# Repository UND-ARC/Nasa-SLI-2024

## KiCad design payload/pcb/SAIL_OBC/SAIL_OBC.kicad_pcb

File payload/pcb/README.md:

# SAIL PCBs

## Files included
- KiCad project file (.kicad_pro)
- KiCad schematic (.kicad_sch) 
- KiCad layout (.kicad_pcb)
- 3D view PNG
- Schematic PDF
- Layout PNG
- Interactive Bill of Materials (.html)

### Onboard Computer (OBC)
- Teensy Microcontroller 
- Sensors
- ESC connectors
- 4-pin JST connector to GPS
- 6-pin JST connector to PDB

### Power Distribution Board (PDB)
- Power input
- 5V and 3.3V Buck Regulators
- External Power Switchj
- Arming Switch
- Pyro Charges
	- Landing Legs
	- Wire Cutter 1
	- Wire Cutter 2
- VCC, 5V, 3.3V, and GND test points
- 6 pin JST connector to OBC

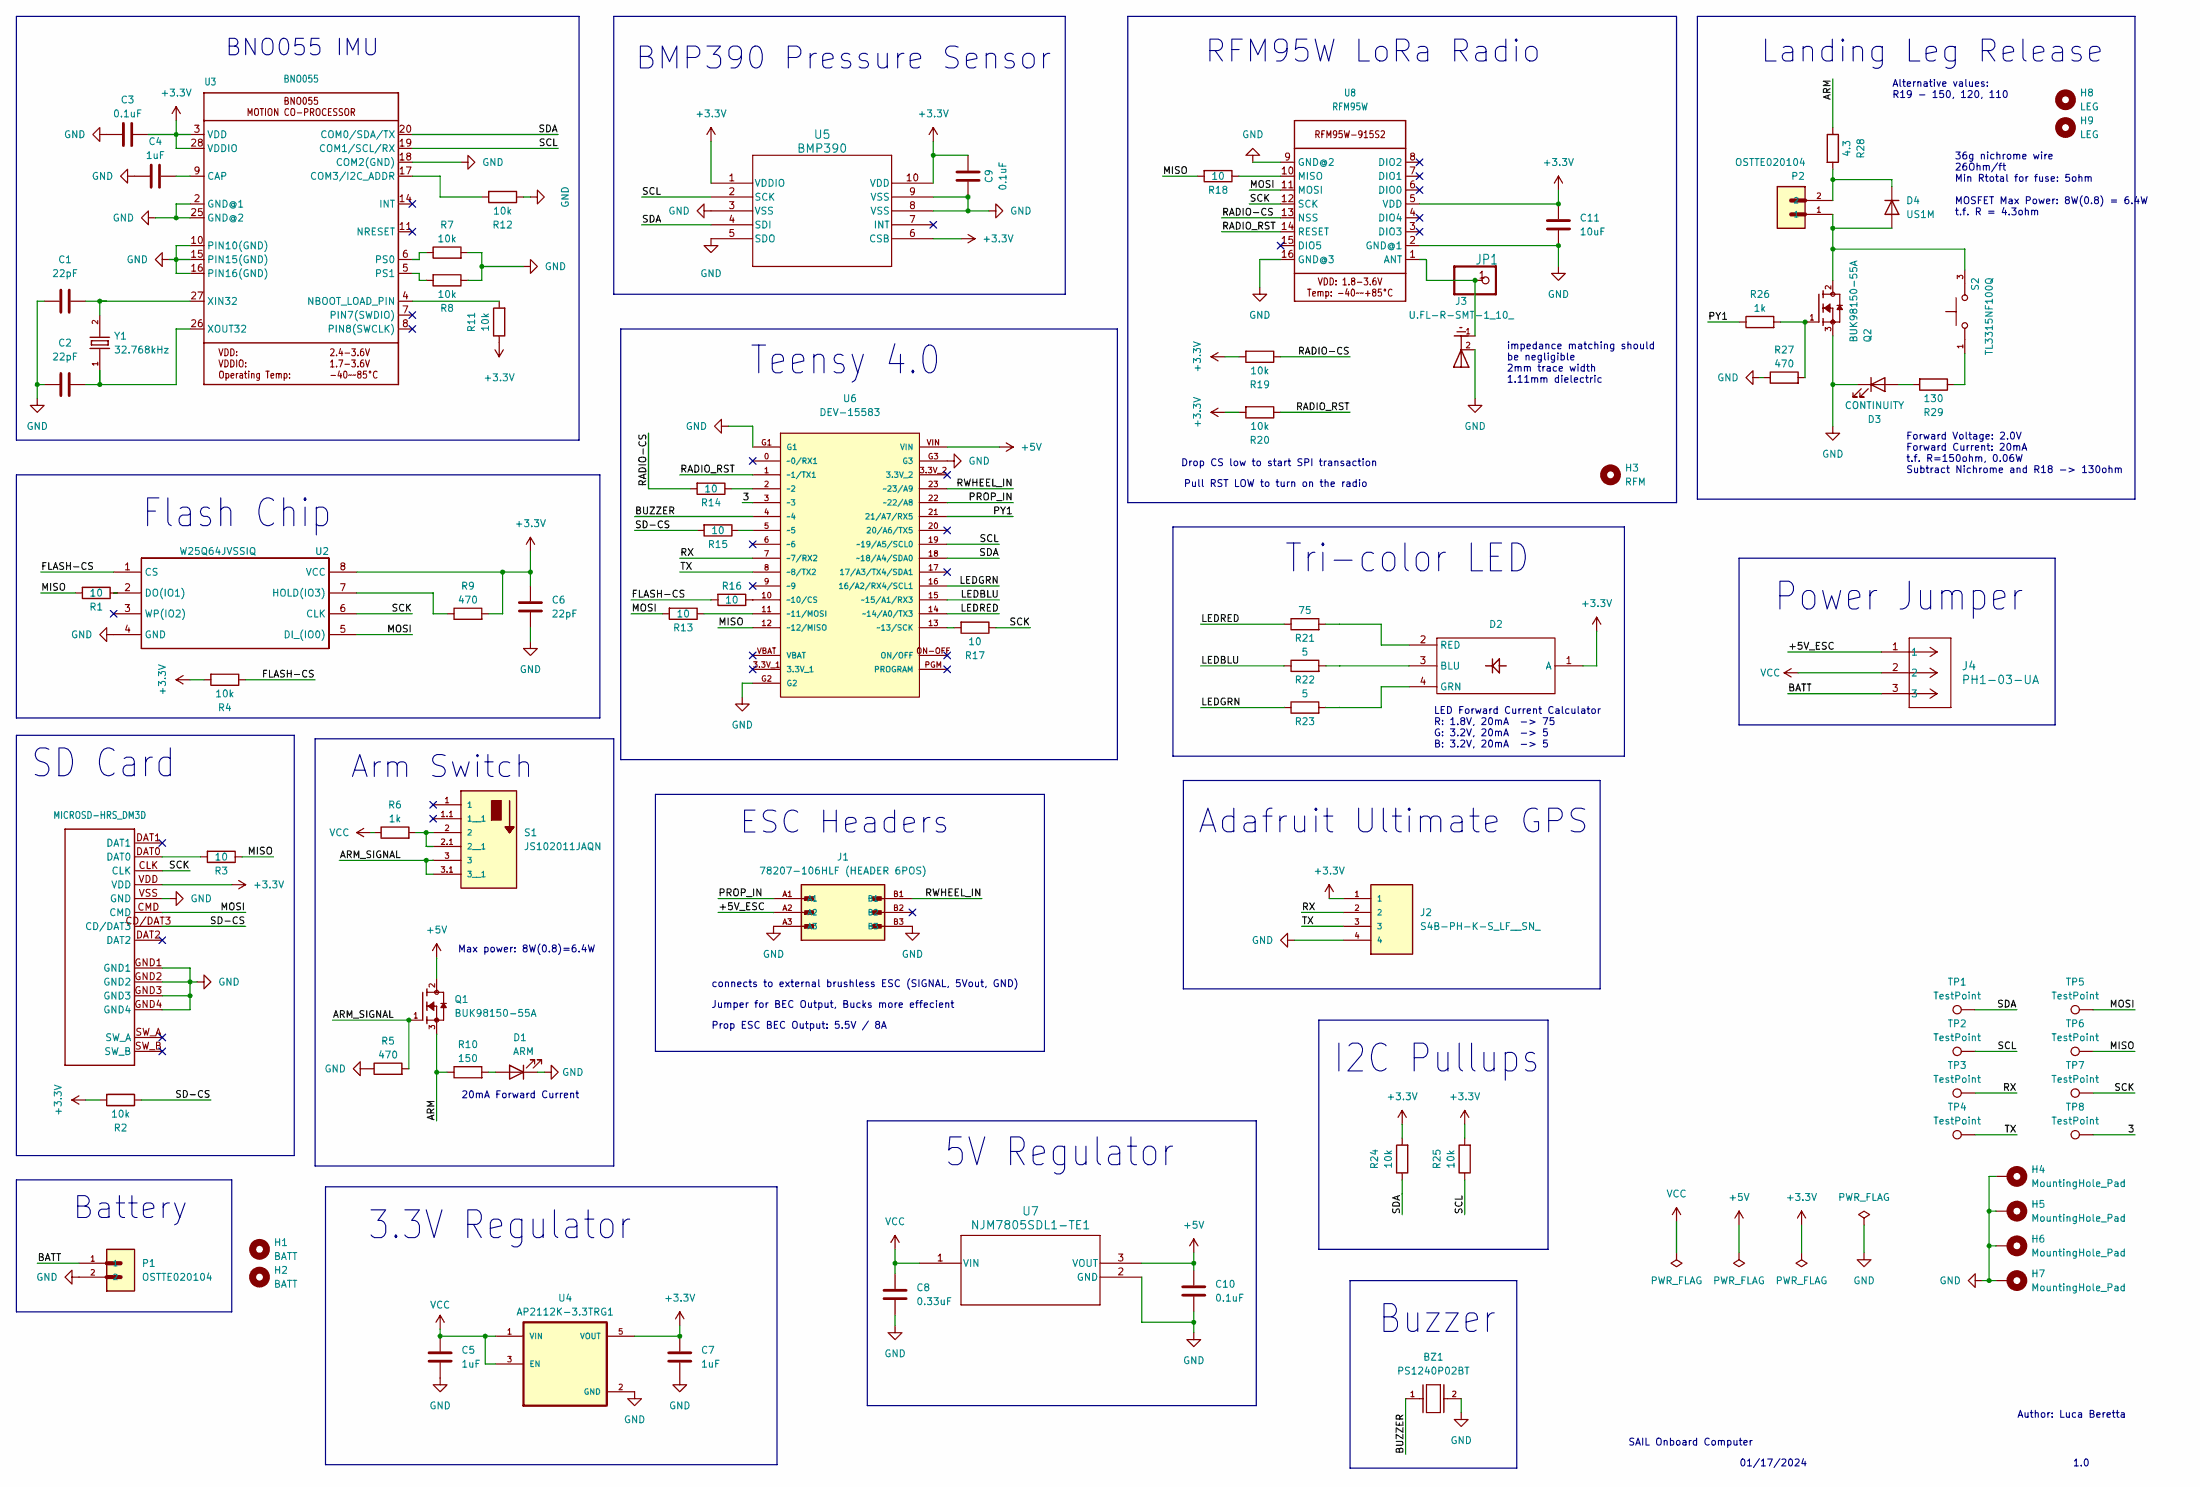
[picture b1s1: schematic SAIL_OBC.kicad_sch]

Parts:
BZ1: PS1240P02BT; BUZZER_XDCR_PS1240P02BT
C1, C2, C6: 22pF; 0805-NO (Capacitor)
C3, C9, C10: 0.1uF; 0805-NO (Capacitor)
C4, C5, C7: 1uF; 0805-NO (Capacitor)
C8: 0.33uF; 0805-NO (Capacitor)
C11: 10uF; 0805-NO (Capacitor)
D1: ARM; LED0805N_CML_(CMD17-21VRDTR8)
D2: TRI-COLOR LED; LED_D5.0mm-4_RGB
D3: CONTINUITY; LED0805N_CML_(CMD17-21VRDTR8)
D4: US1M; D_SMA
H1, H2: BATT; MountingHole_2.7mm_M2.5_ZIPTIE
H3: RFM; MountingHole_2.7mm_M2.5_ZIPTIE
H4, H5, H6, H7: MountingHole_Pad; MountingHole_3mm_Pad
H8, H9: LEG; MountingHole_2.7mm_M2.5_ZIPTIE
J1: 78207-106HLF (HEADER 6POS); AMPHENOL_78207-106HLF
J2: S4B-PH-K-S_LF__SN_; JST_S4B-PH-K-S_LF__SN_
J3: U.FL-R-SMT-1_10_; CONN1_UFL-R_HIR
J4: PH1-03-UA; PinHeader_1x3_P2.54_Drill1.1mm
JP1: HEADER-1X1ROUND; 1X01_ROUND
P1, P2: OSTTE020104; TERMBLOCK_OSTTE020104_3_5MM
Q1, Q2: BUK98150-55A; BUK98150-55ACUF
R1, R3, R13, R14, R15, R16, R17, R18: 10; R_0603_1608Metric_Pad0.98x0.95mm_HandSolder
R2, R7, R8, R11, R12, R19, R20, R24, R25: 10k; 0805-NO-Resistor
R4: 10k; R_0603_1608Metric_Pad0.98x0.95mm_HandSolder
R5, R9, R27: 470; 0805-NO-Resistor
R6, R26: 1k; 0805-NO-Resistor
R10: 150; 0805-NO-Resistor
R21: 75; 0805-NO-Resistor
R22, R23: 5; 0805-NO-Resistor
R28: 4.3; RESC6331X65N
R29: 130; 0805-NO-Resistor
S1: JS102011JAQN; SW_JS102011JAQN
S2: TL3315NF100Q; SW_TL3315NF100Q
TP1, TP2, TP3, TP4, TP5, TP6, TP7, TP8: TestPoint; TestPoint_Pad_2.0x2.0mm
U1: MICROSD-HRS_DM3D
U2: W25Q64JVSSIQ
U3: BNO055; BNO055_SMT
U4: AP2112K-3.3TRG1; SOT95P285X140-5N
U5: BMP390; LGA10_BMP390_BOS
U6: DEV-15583; MODULE_DEV-15583
U7: NJM7805SDL1-TE1; TO-252-3-L1_NMD
U8: RFM95W; RFMHCW_SMT
Y1: 32.768kHz; CRYSTAL_ECS-.327-12.5-34B-TR

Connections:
+3.3V: C3.2, C6.1, C7.1, C9.2, C11.2, D2.1 (A), J2.1, R2.2, R4.2, R9.2, R11.1, R19.2, R20.2, R24.2, R25.2, U1.VDD, U2.8 (VCC), U3.3 (VDD), U3.28 (VDDIO), U4.5 (VOUT), U5.1 (VDDIO), U5.6 (CSB), U5.10 (VDD), U8.5 (VDD)
+5V: C10.2, Q1.2, U6.VIN, U7.3 (VOUT)
/3: TP8.1, U6.3 (~3)
/+5V_ESC: J1.A2, J4.1
/ARM: Q1.3, R10.1, R28.1
/ARM_SIGNAL: Q1.1, R5.2, S1.3, S1.3.1 (3__1)
/BATT: J4.3, P1.1
/BUZZER: BZ1.1, U6.4 (~4)
/FLASH-CS: R4.1, R16.2, U2.1 (CS)
/LEDBLU: R22.1, U6.15 (~15/A1/RX3)
/LEDGRN: R23.1, U6.16 (16/A2/RX4/SCL1)
/LEDRED: R21.1, U6.14 (~14/A0/TX3)
/MISO: R1.2, R3.1, R18.2, TP6.1, U6.12 (~12/MISO)
/MOSI: R13.2, TP5.1, U1.CMD, U2.5 (DI_(IO0)), U8.11 (MOSI)
/PROP_IN: J1.A1, U6.22 (~22/A8)
/PY1: R26.1, U6.21 (21/A7/RX5)
/RADIO-CS: R14.2, R19.1, U8.13 (NSS)
/RADIO_RST: R20.1, U6.1 (~1/TX1), U8.14 (RESET)
/RWHEEL_IN: J1.B1, U6.23 (~23/A9)
/RX: J2.2, TP3.1, U6.7 (~7/RX2)
/SCK: R17.1, TP7.1, U1.CLK, U2.6 (CLK), U8.12 (SCK)
/SCL: R25.1, TP2.1, U3.19 (COM1/SCL/RX), U5.2 (SCK), U6.19 (~19/A5/SCL0)
/SD-CS: R2.1, R15.2, U1.CD/DAT3
/SDA: R24.1, TP1.1, U3.20 (COM0/SDA/TX), U5.4 (SDI), U6.18 (~18/A4/SDA0)
/TX: J2.3, TP4.1, U6.8 (~8/TX2)
GND: BZ1.2, C1.1, C2.1, C3.1, C4.1, C5.2, C6.2, C7.2, C8.1, C9.1, C10.1, C11.1, D1.1 (K), D3.1 (K), H4.1, H5.1, H6.1, H7.1, J1.A3, J1.B3, J2.4, J3.2, P1.2, Q2.3, R5.1, R7.2, R8.1, R12.1, R27.1, U1.GND1, U1.GND2, U1.GND3, U1.GND4, U1.VSS (GND), U2.4 (GND), U3.2 (GND@1), U3.10 (PIN10(GND)), U3.15 (PIN15(GND)), U3.16 (PIN16(GND)), U3.18 (COM2(GND)), U3.25 (GND@2), U4.2 (GND), U5.3 (VSS), U5.5 (SDO), U5.8 (VSS), U5.9 (VSS), U6.G1, U6.G2, U6.G3, U7.2 (GND), U8.2 (GND@1), U8.9 (GND@2), U8.16 (GND@3)
unnamed: D1.2 (A), R10.2
unnamed: D2.3 (BLU), R22.2
unnamed: D2.4 (GRN), R23.2
unnamed: D2.2 (RED), R21.2
unnamed: D3.2 (A), R29.2
unnamed: D4.2 (A), P2.1, Q2.2, S2.3
unnamed: D4.1 (K), P2.2, R28.2
unnamed: Q2.1, R26.2, R27.2
unnamed: R3.2, U1.DAT0
unnamed: R29.1, S2.1
unnamed: R6.2, S1.2, S1.2.1 (2__1)
unnamed: R1.1, U2.2 (DO(IO1))
unnamed: R9.1, U2.7 (HOLD(IO3))
unnamed: C4.2, U3.9 (CAP)
unnamed: R12.2, U3.17 (COM3/I2C_ADDR)
unnamed: R11.2, U3.4 (NBOOT_LOAD_PIN)
unnamed: R7.1, U3.6 (PS0)
unnamed: R8.2, U3.5 (PS1)
unnamed: C1.2, U3.27 (XIN32), Y1.2
unnamed: C2.2, U3.26 (XOUT32), Y1.1
unnamed: R14.1, U6.2 (~2)
unnamed: R15.1, U6.5 (~5)
unnamed: R16.1, U6.10 (~10/CS)
unnamed: R13.1, U6.11 (~11/MOSI)
unnamed: R17.2, U6.13 (~13/SCK)
unnamed: J3.1, JP1.1, U8.1 (ANT)
unnamed: R18.1, U8.10 (MISO)
VCC: C5.1, C8.2, J4.2, R6.1, U4.1 (VIN), U4.3 (EN), U7.1 (VIN)

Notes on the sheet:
3.3V Regulator
Alternative values: R19 - 150, 120, 110
Prop ESC BEC Output: 5.5V / 8A
Max power: 8W(0.8)=6.4W
36g nichrome wire 26Ohm/ft Min Rtotal for fuse: 5ohm MOSFET Max Power: 8W(0.8) = 6.4W t.f. R = 4.3ohm
Flash Chip
BMP390 Pressure Sensor
Battery
Author: Luca Beretta
Buzzer
connects to external brushless ESC (SIGNAL, 5Vout, GND)
SD Card
5V Regulator
LED Forward Current Calculator R: 1.8V, 20mA -> 75 G: 3.2V, 20mA -> 5 B: 3.2V, 20mA -> 5
01/17/2024
Teensy 4.0
Drop CS low to start SPI transaction
Forward Voltage: 2.0V Forward Current: 20mA t.f. R=150ohm, 0.06W Subtract Nichrome and R18 -> 130ohm
Power Jumper
ESC Headers
1.0
BNO055 IMU
SAIL Onboard Computer
RFM95W LoRa Radio
impedance matching should be negligible 2mm trace width 1.11mm dielectric
Arm Switch
Jumper for BEC Output, Bucks more effecient
Pull RST LOW to turn on the radio
Adafruit Ultimate GPS
Landing Leg Release
20mA Forward Current
I2C Pullups
Tri-color LED

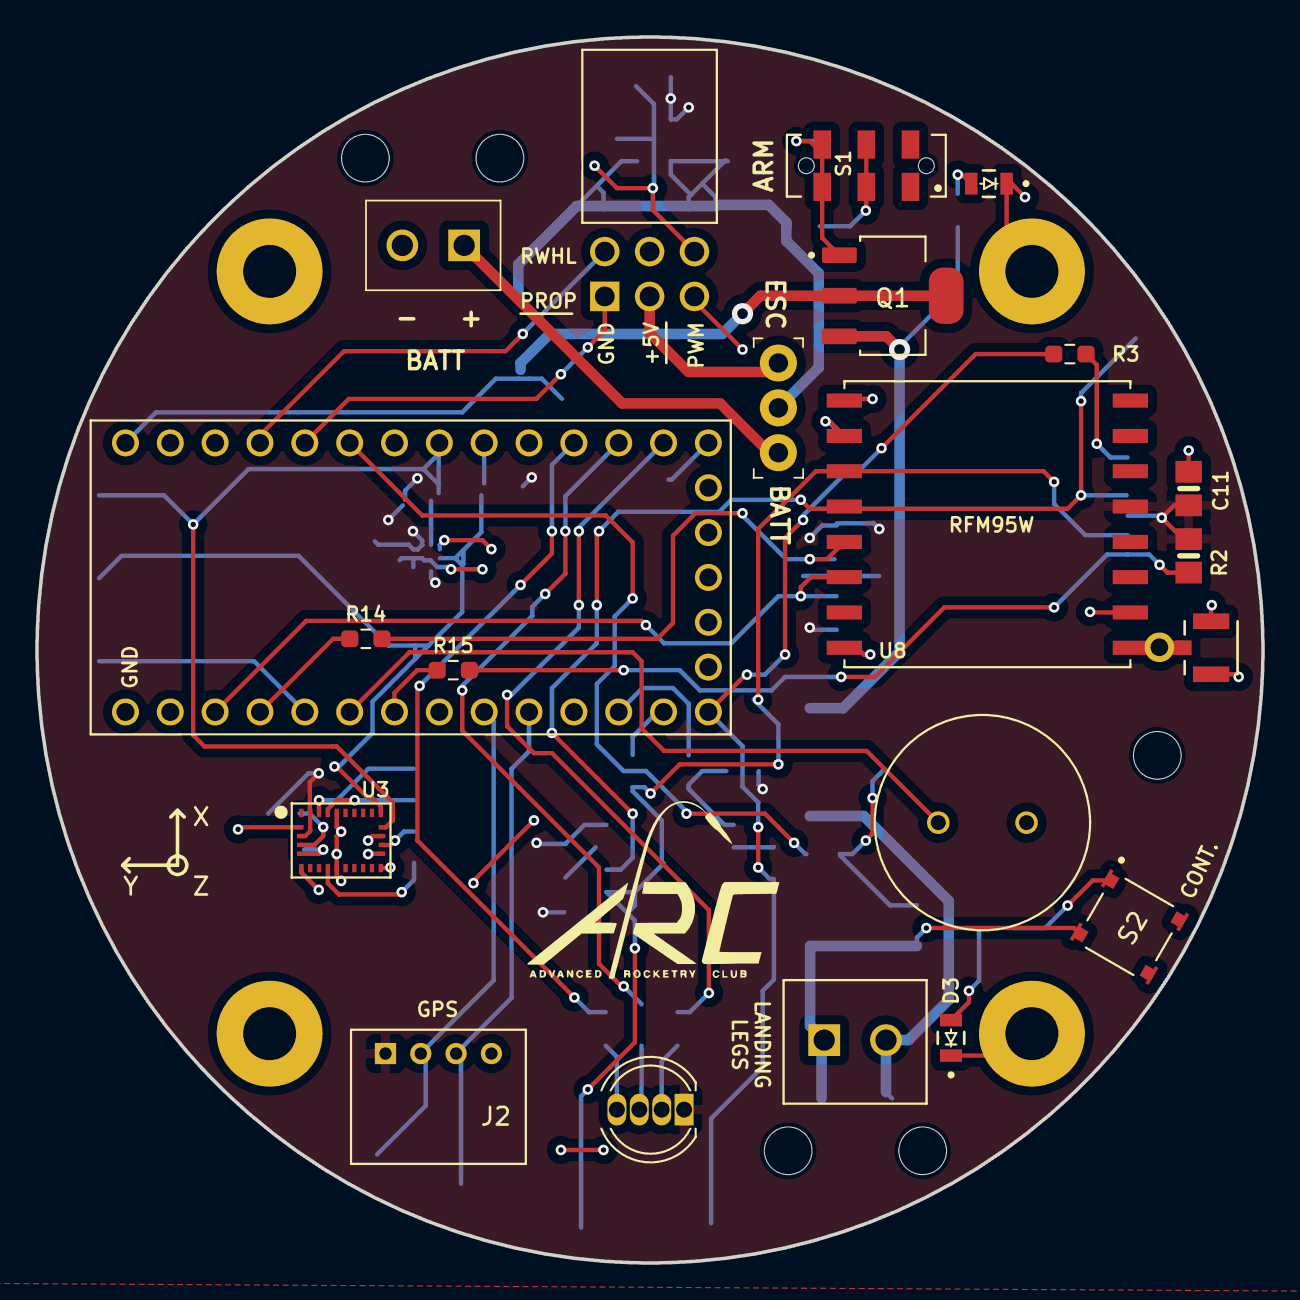
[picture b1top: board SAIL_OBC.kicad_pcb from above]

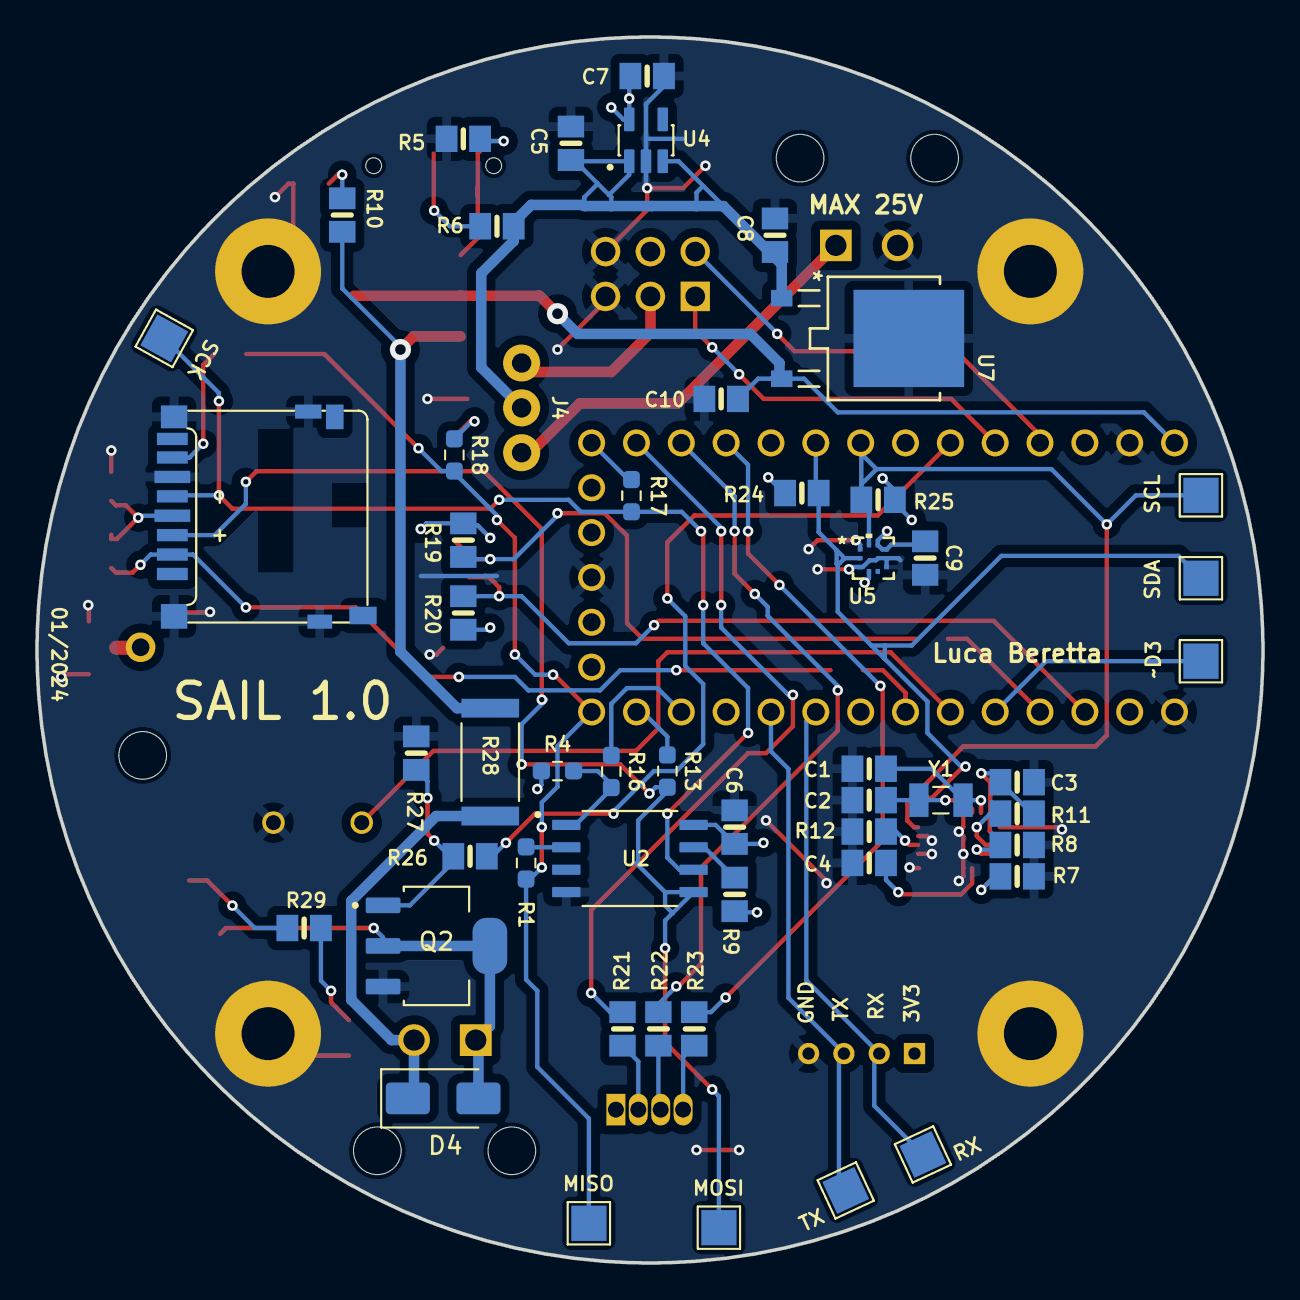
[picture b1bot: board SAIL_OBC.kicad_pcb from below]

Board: 2 copper layers, 69.4 x 69.4 mm, 82 parts (51 on the bottom side), 54 nets.

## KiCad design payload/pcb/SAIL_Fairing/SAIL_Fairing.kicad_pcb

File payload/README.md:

# STEMnauts Atmosphere Independent Lander (SAIL)

UND ARC SAIL Payload Module

## NASA Student Launch Objective

SAIL is an in-air deployable payload capable of safely retaining and recovering a group of 4 STEMnauts in a unique predetermined orientation without the use of a parachute or streamer or chemical energetics below 500 ft AGL. The landing shall occur under acceptable descent and landing parameters for the safe recovery of human beings.

## Description

The Advanced Rocketry Club of the University of North Dakota is designing a UAS-style payload that will deploy upon descent, autonomously land under acceptable parameters, and log flight data. The final electronics package shall be a custom 2x2 in Printed Circuit Board (PCB) that will be mounted on the SAIL payload with various connections to the battery, safety switch, landing leg release, and Electronic Speed Controllers (ESCs).

## Getting Started

### Hardware
- Teensy 4.0 Microcontroller
- BNO055 IMU
- BMP390 Pressure Sensor
- SPI Flash Chip
- MicroSD Card Holder
- Adafruit Ultimate GPS
- RFM95W 915MHz Radio Transceiver
- Xnova 4025 1120 KV Brushless Motor
- iFlight XING-E Pro 2207 1800KV Brushless Motor
- V-Good RC 32-Bit 120A 2-8S Brushless ESC
- Lumenier 36A BLHeli_32 32bit ESC
- 9V Battery
- 6S 2200mAh LiPo Battery

### Software
- C++ w/ Arduino IDE
- PCB designed in KiCad 7.0

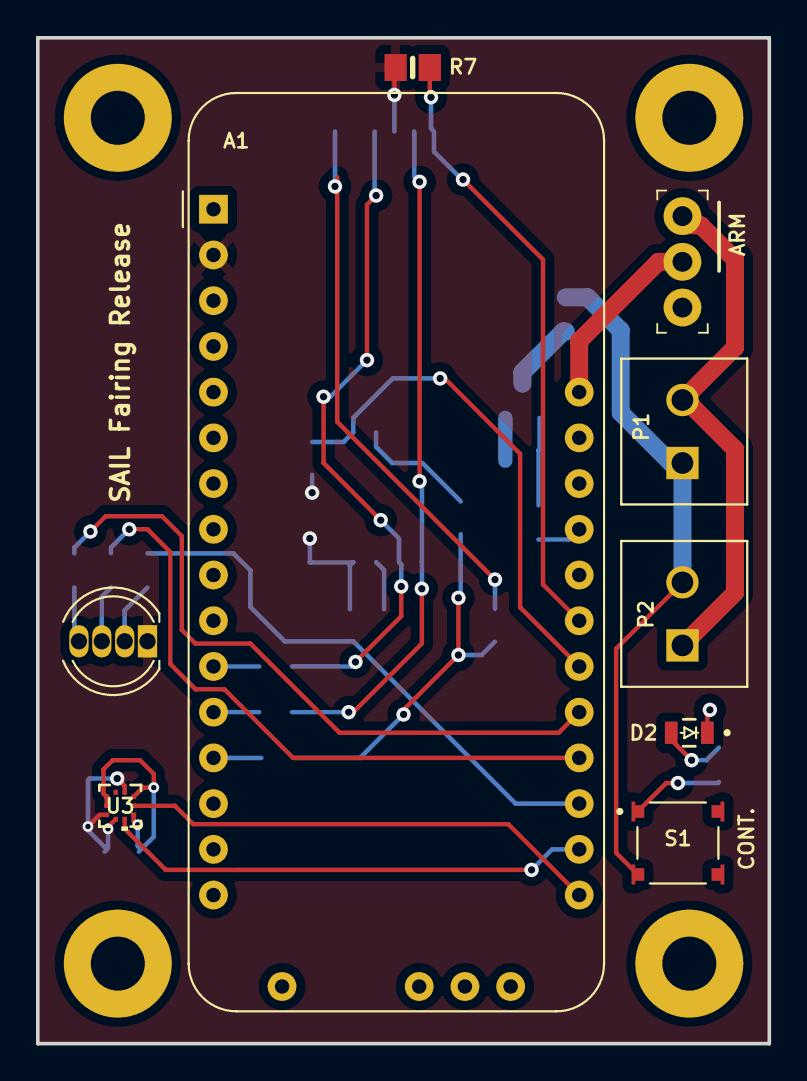
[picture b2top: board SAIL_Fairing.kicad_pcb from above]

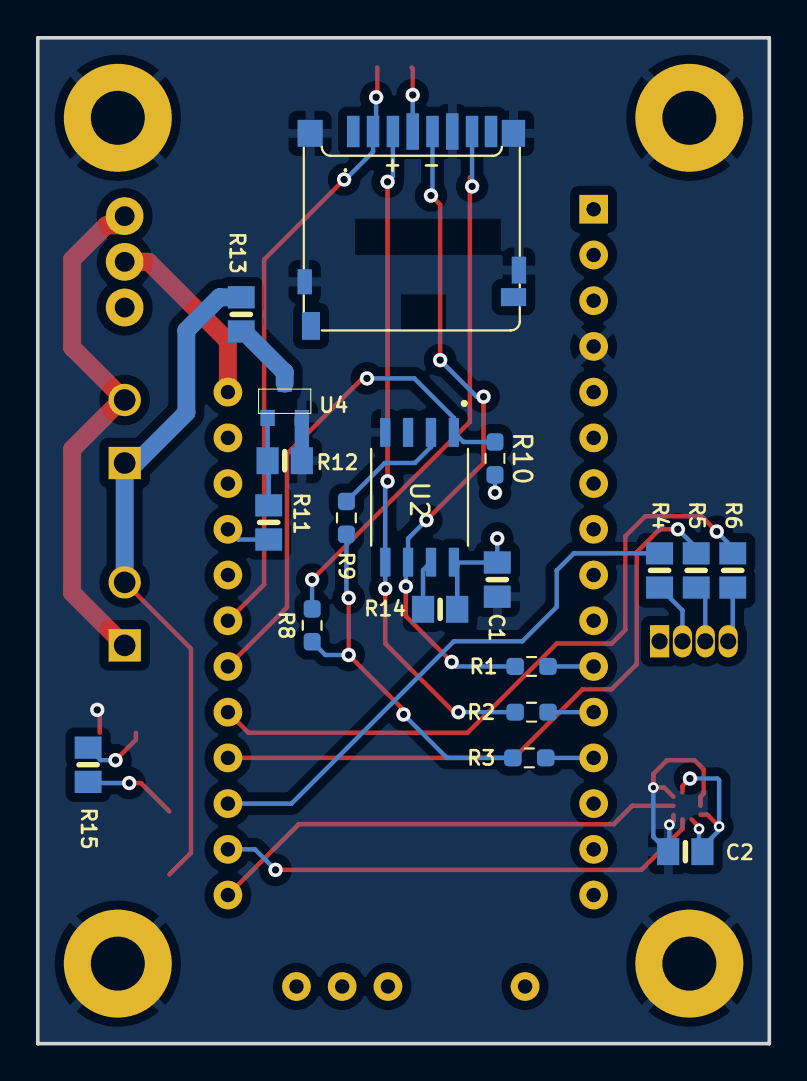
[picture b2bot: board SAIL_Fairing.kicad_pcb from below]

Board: 2 copper layers, 40.6 x 55.9 mm, 32 parts (19 on the bottom side), 29 nets.

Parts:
A1: Adafruit_Feather_M0_RFM9x_LoRa_Radio; Adafruit_Feather_M0_RFM
C1: 22pF; 0805-NO (Capacitor)
C2: 0.1uF; 0805-NO (Capacitor)
D1: TRI-COLOR LED; LED_D5.0mm-4_RGB
D2: LED; LED0805N_CML_(CMD17-21VRDTR8)
H1, H2, H3, H4: MountingHole_Pad; MountingHole_3mm_Pad
J1: PH1-03-UA; PinHeader_1x3_P2.54_Drill1.1mm
P1, P2: OSTTE020104; TERMBLOCK_OSTTE020104_3_5MM
R1, R2, R3, R8, R9: 10; R_0603_1608Metric_Pad0.98x0.95mm_HandSolder
R4: 75; 0805-NO-Resistor
R5, R6: 5; 0805-NO-Resistor
R7: 10k; 0805-NO-Resistor
R10: 10k; R_0603_1608Metric_Pad0.98x0.95mm_HandSolder
R11: 1k; 0805-NO-Resistor
R12, R14: 470; 0805-NO-Resistor
R13: 1; 0805-NO-Resistor
R15: 82; 0805-NO-Resistor
S1: TL3315NF100Q; SW_TL3315NF100Q
U1: MICROSD-HRS_DM3D
U2: W25Q64JVSSIQ
U3: BMP390; LGA10_BMP390_BOS
U4: DMN3051L-7

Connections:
+3.3V: A1.2 (3V3), C1.1, C2.1, D1.1 (A), R7.2, R10.2, R14.2, U1.VDD, U2.8 (VCC), U3.1 (VDDIO), U3.6 (CSB), U3.10 (VDD)
/ARM: J1.3, P1.2, P2.1
/CUT: A1.25 (D13), R11.1
/FLASH-CS: A1.22 (D10), R10.1, U2.1 (CS)
/LEDBLU: A1.20 (D6), R5.1
/LEDGRN: A1.21 (D9), R6.1
/LEDRED: A1.19 (D5), R4.1
/MISO: R3.2, R8.1, R9.2
/MOSI: R2.2, U1.CMD, U2.5 (DI_(IO0))
/SCK: R1.2, U1.CLK, U2.6 (CLK)
/SCL: A1.18 (SCL/D21), U3.2 (SCK)
/SD-CS: A1.23 (D11), R7.1, U1.CD/DAT3
/SDA: A1.17 (SDA/D20), U3.4 (SDI)
/VBAT: A1.28 (VBAT), J1.2
GND: A1.4 (GND), C1.2, C2.2, D2.1 (K), H1.1, H2.1, H3.1, H4.1, R12.1, U1.GND1, U1.GND2, U1.GND3, U1.GND4, U1.VSS (GND), U2.4 (GND), U3.3 (VSS), U3.5 (SDO), U3.8 (VSS), U3.9 (VSS), U4.BOTR (SOURCE)
unnamed: A1.13 (MISO/D22), R3.1
unnamed: A1.12 (MOSI/D23), R2.1
unnamed: A1.11 (SCK/D24), R1.1
unnamed: D1.3 (BLU), R5.2
unnamed: D1.4 (GRN), R6.2
unnamed: D1.2 (RED), R4.2
unnamed: D2.2 (A), R15.1
unnamed: P1.1, P2.2, R13.2, S1.3
unnamed: R8.2, U1.DAT0
unnamed: R15.2, S1.1
unnamed: R9.1, U2.2 (DO(IO1))
unnamed: R14.1, U2.7 (HOLD(IO3))
unnamed: R13.1, U4.TIP (DRAIN)
unnamed: R11.2, R12.2, U4.BOTL (GATE)

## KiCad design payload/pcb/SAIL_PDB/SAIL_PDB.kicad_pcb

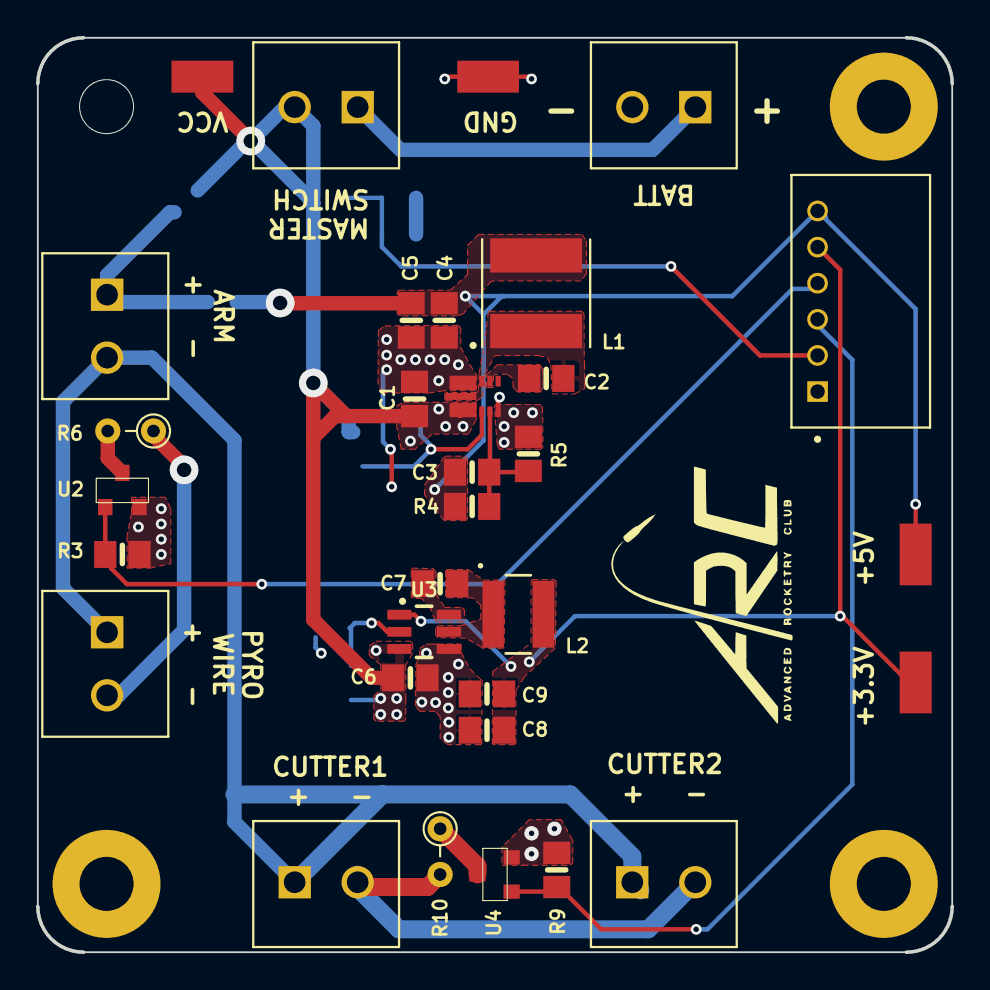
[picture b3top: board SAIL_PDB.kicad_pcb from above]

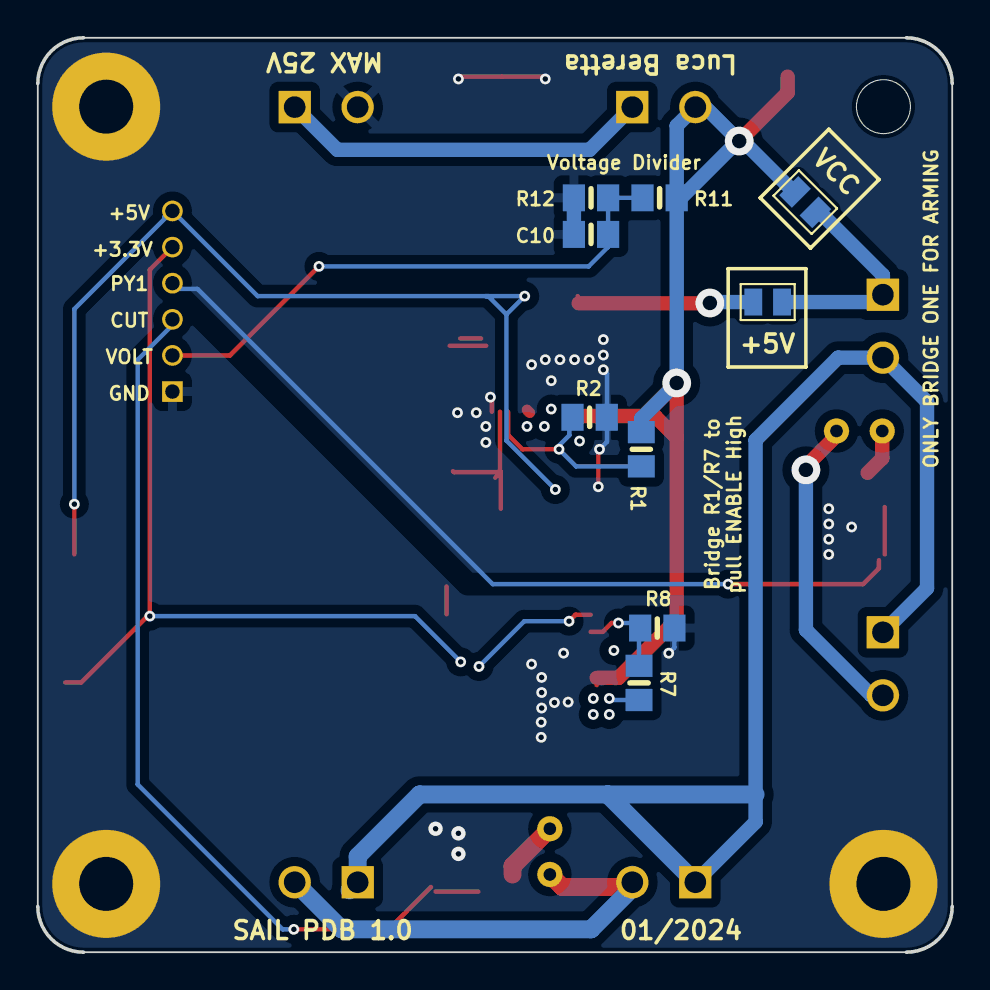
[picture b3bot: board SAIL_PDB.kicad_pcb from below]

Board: 4 copper layers, 50.8 x 50.8 mm, 45 parts (9 on the bottom side), 21 nets.

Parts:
C1, C6: 10uF; 0805-NO (Capacitor)
C2, C7: 0.1uF; 0805-NO (Capacitor)
C3: 4.7pF; 0805-NO (Capacitor)
C4, C5, C8, C9: 22uF; 0805-NO (Capacitor)
C10: 1uF; 0805-NO (Capacitor)
H1: MountingHole_Pad; MountingHole_3mm
H2, H3, H4: MountingHole_Pad; MountingHole_3mm_Pad
J1: 440055-6_6POS_2MM; TE_440055-6_6POS_2MM
JP1, JP3: Jumper_2_Open; SolderJumper-2_P1.3mm_Open_Pad1.0x1.5mm
L1: 6.8uH; INDUCTOR_VLS6045EX-6.8uH
L2: 4.7uH; IND_NRS4018T4R7MDGJ_4.7uH
P1, P2, P3, P4, P5, P6: OSTTE020104; TERMBLOCK_OSTTE020104_3_5MM
R1, R7: 68k; 0805-NO-Resistor
R2, R8: 3.6k; 0805-NO-Resistor
R3, R9, R12: 470; 0805-NO-Resistor
R4: 158k; 0805-NO-Resistor
R5: 30k; 0805-NO-Resistor
R6: 2.7; R_Axial_DIN0204_L3.6mm_D1.6mm_P2.54mm_Vertical
R10: 3.9; R_Axial_DIN0204_L3.6mm_D1.6mm_P2.54mm_Vertical
R11: 3900; 0805-NO-Resistor
TP1, TP2, TP3, TP4: 5015; KEYSTONE_5015_TEST
U1: AP63357_(SparkFun_Buck_Regulator_5V); AP63356 (V-DFN3020-13)
U2, U4: DMN3051L-7
U3: AP63203; BUCK_AP63203_3.3_SPARKFUN

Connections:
+3.3V: C8.1, C9.1, J1.5, L2.2, TP3.TP, U3.1 (FB)
+5V: C3.1, C4.1, C5.1, J1.6, JP1.1 (A), L1.2, R4.1, TP2.TP
/ARM: P3.2, P4.1, P5.1, P6.1
/BATT+: P1.1, P2.1
/BUCK1_BST: C2.1, U1.6 (BST)
/BUCK1_FB: C3.2, R4.2, R5.1, U1.3 (FB)
/BUCK1_SW: C2.2, L1.1, U1.9 (SW)
/BUCK2_BST: C7.1, U3.6 (BST)
/BUCK2_EN: R7.1, R8.2, U3.2 (EN)
/BUCK2_SW: C7.2, L2.1, U3.5 (SW)
/PY1: J1.4, R3.2, U2.BOTL (GATE)
/PYROCUT: J1.3, R9.2, U4.BOTL (GATE)
/VOLTAGE: C10.1, J1.2, R11.2, R12.2
GND: C1.2, C4.2, C5.2, C6.2, C8.2, C9.2, C10.2, H2.1, H3.1, H4.1, J1.1, P1.2, R2.2, R3.1, R5.2, R8.1, R9.1, R12.1, TP4.TP, U1.4 (COMP), U1.8 (GND), U2.BOTR (SOURCE), U3.4 (GND), U4.BOTR (SOURCE)
unnamed: JP1.2 (B), JP3.2 (B), P3.1
unnamed: P4.2, R6.1
unnamed: P5.2, P6.2, R10.2
unnamed: R1.2, R2.1, U1.2 (EN)
unnamed: R6.2, U2.TIP (DRAIN)
unnamed: R10.1, U4.TIP (DRAIN)
VCC: C1.1, C6.1, JP3.1 (A), P2.2, R1.1, R7.2, R11.1, TP1.TP, U1.1 (VIN), U3.3 (VIN)

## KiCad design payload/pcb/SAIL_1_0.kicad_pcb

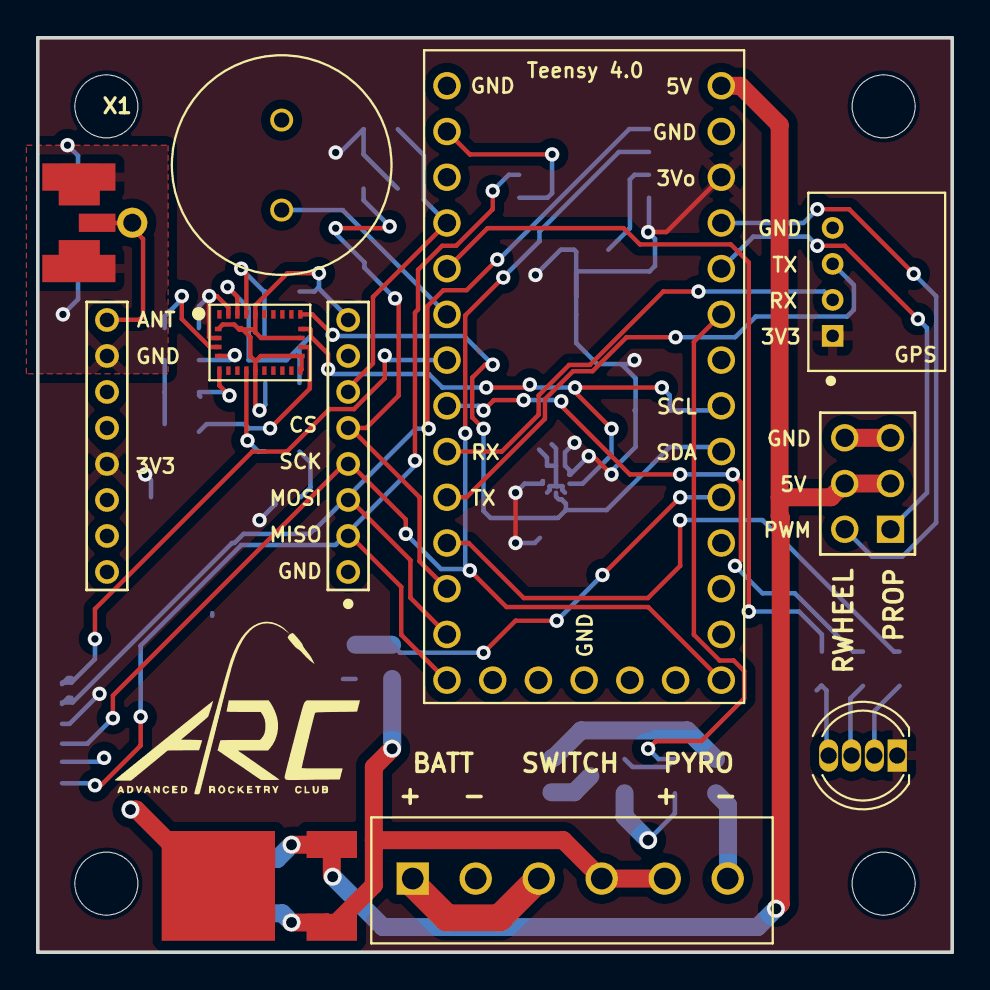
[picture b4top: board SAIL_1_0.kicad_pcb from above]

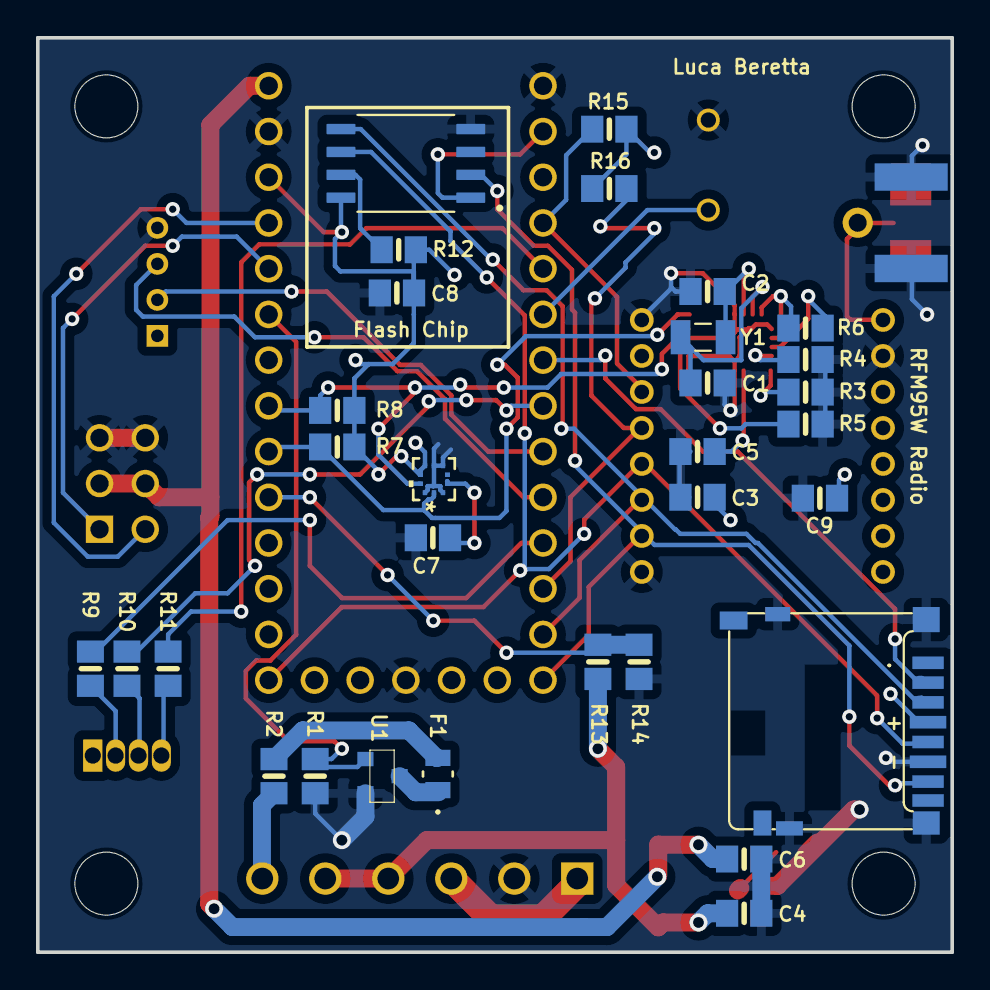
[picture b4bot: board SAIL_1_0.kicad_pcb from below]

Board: 2 copper layers, 50.8 x 50.8 mm, 46 parts (31 on the bottom side), 39 nets.

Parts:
BZ1: PS1240P02BT; BUZZER_XDCR_PS1240P02BT
C1, C2, C8: 22 pF; 0805-NO (Capacitor)
C3, C6: 0.1 uF; 0805-NO (Capacitor)
C4: 0.33 uF; 0805-NO (Capacitor)
C5: 1 uF; 0805-NO (Capacitor)
C7: 100 nF; 0805-NO (Capacitor)
C9: 10 uF; 0805-NO (Capacitor)
D1: TRI-COLOR LED; LED_D5.0mm-4_RGB
F1: MFU0805FF05000P100; FUS_VISHAY_MFU0805_VIS_5A
H1, H2, H3, H4: MountingHole; MountingHole_3.5mm
J1: TERMBLOCK_OSTTE060104
J2: RFM95 Mount; RFM95 SMT THT Mount
J3: HEADER_M20-9950345_90_2x3; HEADER_PH2-06-UA_ADM_2x3
J4: S4B-PH-K-S; JST_S4B-PH-K-S_LF__SN_
JP1: HEADER-1X1ROUND; 1X01_ROUND
R1: 470; 0805-NO-Resistor
R2: 4.7; 0805-NO-Resistor
R3, R4, R5, R6, R7, R8, R15, R16: 10k; 0805-NO-Resistor
R9: 40; 0805-NO-Resistor
R10, R11: 1; 0805-NO-Resistor
R12: 10M; 0805-NO-Resistor
R13: 2000; 0805-NO-Resistor
R14: 510; 0805-NO-Resistor
U1: DMN3051L-7
U2: BNO055_SMT
U3: MICROSD-HRS_DM3D
U4: BMP390; LGA10_BMP390_BOS
U5: W25Q64JVSSIQ
U6: DEV-15583; MODULE_DEV-15583
VR1: L7805CDT
X1: uFL/SMA; SMA_EDGELAUNCH_UFL
Y1: CRYSTAL_32.768kHz; CRYSTAL_ECS-.327-12.5-34B-TR

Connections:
+3.3V: C3.2, C7.1, C8.1, C9.2, D1.1 (A), J2.13 (3.3V), J4.1, R6.1, R7.2, R8.2, R12.2, R15.1, R16.1, U2.3 (VDD), U2.28 (VDDIO), U3.VDD, U4.1 (VDDIO), U4.6 (CSB), U4.10 (VDD), U5.8 (VCC), U6.3.3V_2
+5V: C6.2, J3.3, J3.4, U6.VIN, VR1.OUTPUT
+9V: C4.2, J1.4, J1.5, R13.1, VR1.INPUT
/BATT+: J1.1, J1.3
/BUZZER: BZ1.1, U6.4 (~4)
/FLASH-CS: U5.1 (CS), U6.0 (~0/RX1)
/LEDBLU: R10.1, U6.6 (~6)
/LEDGRN: R11.1, U6.3 (~3)
/LEDRED: R9.1, U6.9 (~9)
/MISO: J2.2 (MISO), U3.DAT0, U5.2 (DO(IO1)), U6.12 (~12/MISO)
/MOSI: J2.3 (MOSI), U3.CMD, U5.5 (DI_(IO0)), U6.11 (~11/MOSI)
/PROP_IN: J3.1, U6.22 (~22/A8)
/PY1: R1.2, U1.BOTL (GATE), U6.21 (21/A7/RX5)
/RADIO-CS: J2.5 (NSS), R16.2, U6.10 (~10/CS)
/RADIO_RST: J2.6 (RESET), R15.2, U6.2 (~2)
/RWHEEL_IN: J3.2, U6.23 (~23/A9)
/RX: J4.2, U6.7 (~7/RX2)
/SCK: J2.4 (SCK), U3.CLK, U5.6 (CLK), U6.13 (~13/SCK)
/SCL: R8.1, U2.19 (COM1/SCL/RX), U4.2 (SCK), U6.19 (~19/A5/SCL0)
/SD-CS: U3.CD/DAT3, U6.5 (~5)
/SDA: R7.1, U2.20 (COM0/SDA/TX), U4.4 (SDI), U6.18 (~18/A4/SDA0)
/TX: J4.3, U6.8 (~8/TX2)
/VOLTAGE: R13.2, R14.2, U6.17 (17/A3/TX4/SDA1)
GND: BZ1.2, C1.1, C2.1, C3.1, C4.1, C5.1, C6.1, C7.2, C8.2, C9.1, J1.2, J2.1 (GND), J2.8 (GND), J2.10 (GND), J3.5, J3.6, J4.4, R1.1, R3.1, R4.1, R5.1, R14.1, U1.BOTR (SOURCE), U2.2 (GND@1), U2.10 (PIN10(GND)), U2.15 (PIN15(GND)), U2.16 (PIN16(GND)), U2.18 (COM2(GND)), U2.25 (GND@2), U3.GND1, U3.GND2, U3.GND3, U3.GND4, U3.VSS (GND), U4.3 (VSS), U4.5 (SDO), U4.8 (VSS), U4.9 (VSS), U5.4 (GND), U6.G1, U6.G2, U6.G3, VR1.GND (GROUND), X1.GND@1 (GND1), X1.GND@2 (GND2), X1.GND@3 (GND3), X1.GND@4 (GND4)
unnamed: D1.3 (BLU), R10.2
unnamed: D1.4 (GRN), R11.2
unnamed: D1.2 (RED), R9.2
unnamed: F1.2, R2.2
unnamed: J1.6, R2.1
unnamed: J2.9 (ANT), JP1.1, X1.P (ANT)
unnamed: F1.1, U1.TIP (DRAIN)
unnamed: C5.2, U2.9 (CAP)
unnamed: R5.2, U2.17 (COM3/I2C_ADDR)
unnamed: R6.2, U2.4 (NBOOT_LOAD_PIN)
unnamed: R3.2, U2.6 (PS0)
unnamed: R4.2, U2.5 (PS1)
unnamed: C1.2, U2.27 (XIN32), Y1.2
unnamed: C2.2, U2.26 (XOUT32), Y1.1
unnamed: R12.1, U5.7 (HOLD(IO3))

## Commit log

2023-08-30 Added blank openrocket file
2023-09-11 New OpenRocket
2023-09-11 New New OpenRocket
2023-09-11 New New New OpenRocket
2023-09-11 DATA
2023-09-11 NEW AND BETTER
2023-10-19 testing discord
2023-10-24 Stripe Info
2023-10-25 new payload local
2023-11-09 Added NASA scale rocket
2023-11-29 Adjusted length
2023-12-10 updated the open rocket
2023-12-10 another push
2023-12-11 made openrocket better
2023-12-19 Add files via upload
    Added SAIL payload files
2023-12-22 Scale launch data added
2023-12-23 Update BMP390_I2C.ino
    Commented out SPI
2023-12-23 Add files via upload
    BNO055 sensorapi example modified for Teensy.
    Note: comment out
    /* Reset */
    write8(BNO055_SYS_TRIGGER_ADDR, 0x20); in .cpp library
2023-12-23 Delete payload/test/BNO055_RAW.ino
    deleted for now
2023-12-23 Update BNO055_sensorapi_Teensy.ino
    Software writing
2023-12-23 Update BlipTestCode_ModifiedForSAIL.ino
    added bno055 diagnostics
2023-12-23 Add files via upload
    BNO055 sensorapi exaple modified for SAIL program. (For testing individual sensor)
    I believe this uses sensor fusion so will need raw data example
2023-12-23 Update BlipTestCode_ModifiedForSAIL.ino
    replaced bno055 section with raw data example modified for SAIL program
2023-12-27 Add files via upload
    SAIL Startup Diagnostics
    Tested with Serial Monitor but not with all components
2023-12-28 Add files via upload
    Tested with Serial Monitor and breakout boards
    RFM95 needs tuning
2023-12-28 Delete payload/test/BlipTestCode_ModifiedForSAIL.ino
    Replaced by SAIL_diagnostics
2023-12-28 Delete payload/test/SAIL_testCode.ino
    outdated
2024-01-04 Reorganiztion
    Reorganized files, added psuedocode for propeller and reaction wheel
2024-01-07 Scale flight analysis
2024-01-07 Updated openrocket
2024-01-07 New plot comparison
2024-01-07 Added google sheet of analysis (converted to xlsx)
2024-01-08 Updated upper body tube size
2024-01-08 updated the stuff
2024-01-08 matlab for lateral distance
2024-01-17 PCB update
    Updated pcb files, schematic pdf, layout png, empty footprints file
2024-01-18 Added 3D view images
2024-01-18 Added interactive BOM
    .html files
2024-01-20 Updated PCBs
2024-01-21 Updated pcb files
2024-01-21 Updated PCBs
    im dumb
2024-01-23 Added pinouts and test code
    Control System Test Code
2024-01-27 SAIL_FSM
    finite state machine
2024-01-29 FSM update
2024-01-29 more updates
2024-01-30 Update GS and Prop
2024-02-02 Updated code
    Added PulsePosition library
2024-02-03 Added MATLAB models
    Control System and BLDC Speed Control (to implement in Control System)
2024-02-28 ESC test
2024-02-28 120A ESC test works
2024-03-03 New fin design to accomodate available materials
2024-03-04 Flight data from full scale launch
2024-03-04 Openrocket update and full scale flight analysis
2024-03-18 DUAL ESC WORKING
2024-03-19 Create Dual_ESC_test_working.ino
    took out high throttle, still works
2024-03-23 GroundStation and Fairing redo
    Redid code. Needs to be tested
2024-03-23 Updated Pinouts + Reorg
2024-03-23 Renaming
    SAIL_Diagnostics is now renamed to SAIL_OBC
2024-03-24 Update SAIL_GroundStation.ino
    Feather m0 has digital pins pulled high. code adjusted to reflect. tested with arm, go, and force open button switch
2024-03-24 Update SAIL_Fairing.ino
    Not fully tested. But for reference
2024-03-24 more test
2024-03-25 Update SAIL_OBC.ino
    Cleaned up a little bit. Still need to complete rfm, add logging (with timestamping). Will add ESC code once these are added.
2024-03-26 Update SAIL_Fairing.ino
    optimized leds
2024-03-26 RADIOS WORK!
    Ground and Fairing are a chatty bunch
2024-03-27 Fairing altimeter + radio only code
